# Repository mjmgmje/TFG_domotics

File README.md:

# TFG_domotics
To learn everything about the project, you should read the TFG_domotic.pdf document

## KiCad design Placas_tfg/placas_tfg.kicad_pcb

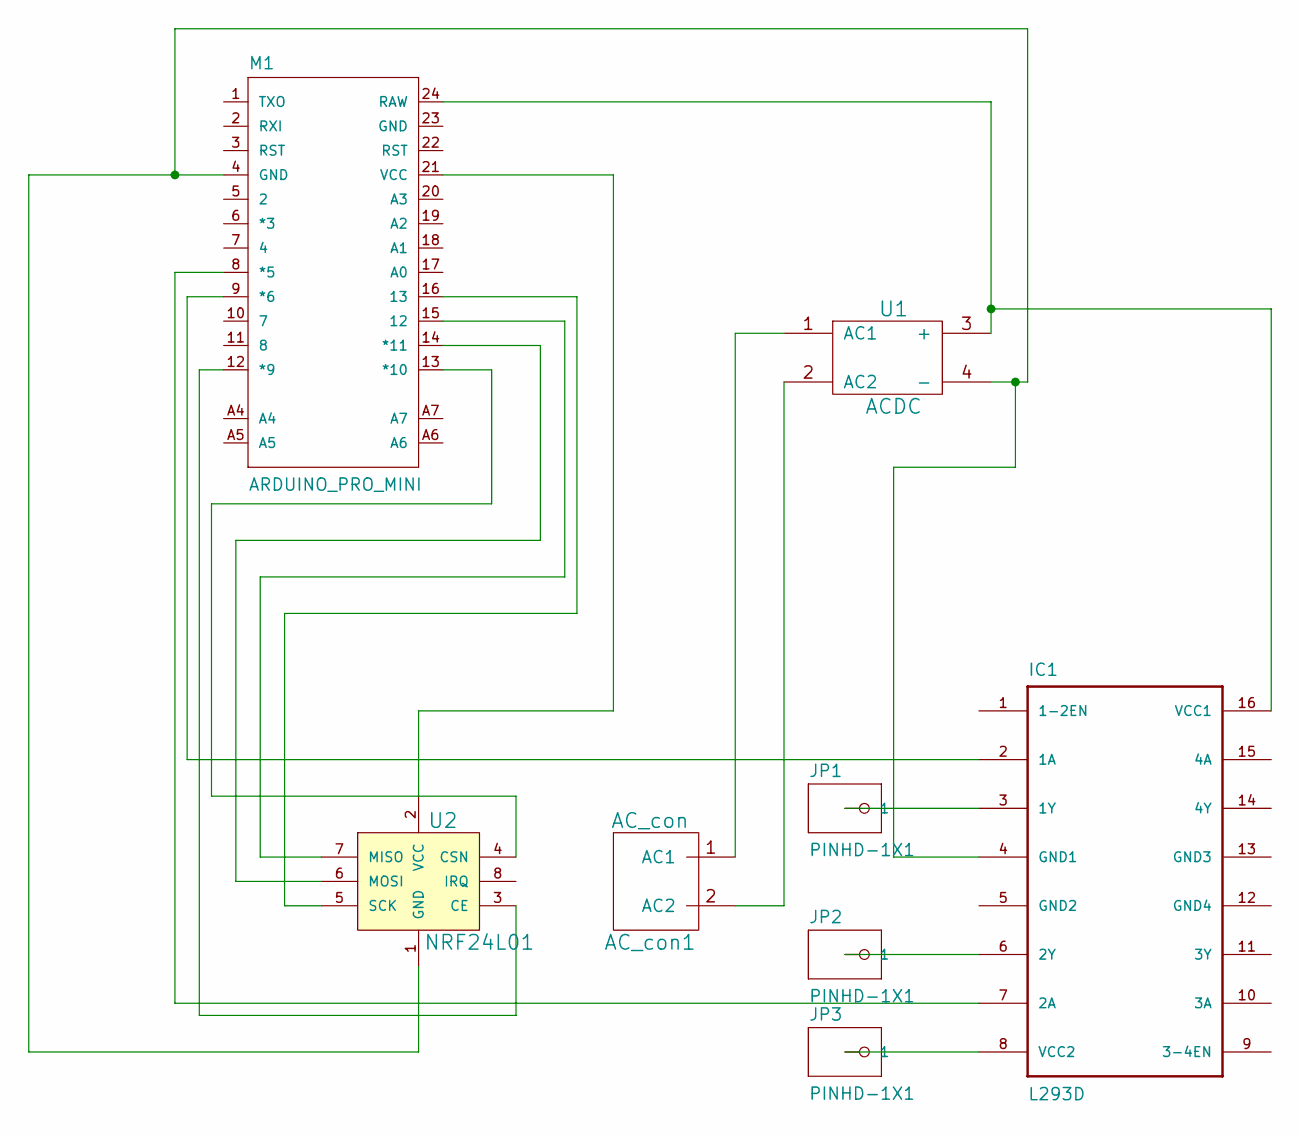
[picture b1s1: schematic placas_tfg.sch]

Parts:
AC_con1: AC_con
IC1: L293D; DIL16
JP1, JP2, JP3: PINHD-1X1; 1X01
M1: ARDUINO_PRO_MINI
U1: ACDC
U2: NRF24L01

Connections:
unnamed: AC_con1.1 (AC1), U1.1 (AC1)
unnamed: AC_con1.2 (AC2), U1.2 (AC2)
unnamed: IC1.2 (1A), M1.9 (*6)
unnamed: IC1.3 (1Y), JP1.1
unnamed: IC1.4 (GND1), M1.4 (GND), U1.4 (-), U2.1 (GND)
unnamed: IC1.6 (2Y), JP2.1
unnamed: IC1.7 (2A), M1.8 (*5)
unnamed: IC1.8 (VCC2), JP3.1
unnamed: IC1.16 (VCC1), M1.24 (RAW), U1.3 (+)
unnamed: M1.12 (*9), U2.3 (CE)
unnamed: M1.13 (*10), U2.4 (CSN)
unnamed: M1.14 (*11), U2.6 (MOSI)
unnamed: M1.15 (12), U2.7 (MISO)
unnamed: M1.16 (13), U2.5 (SCK)
unnamed: M1.21 (VCC), U2.2 (VCC)

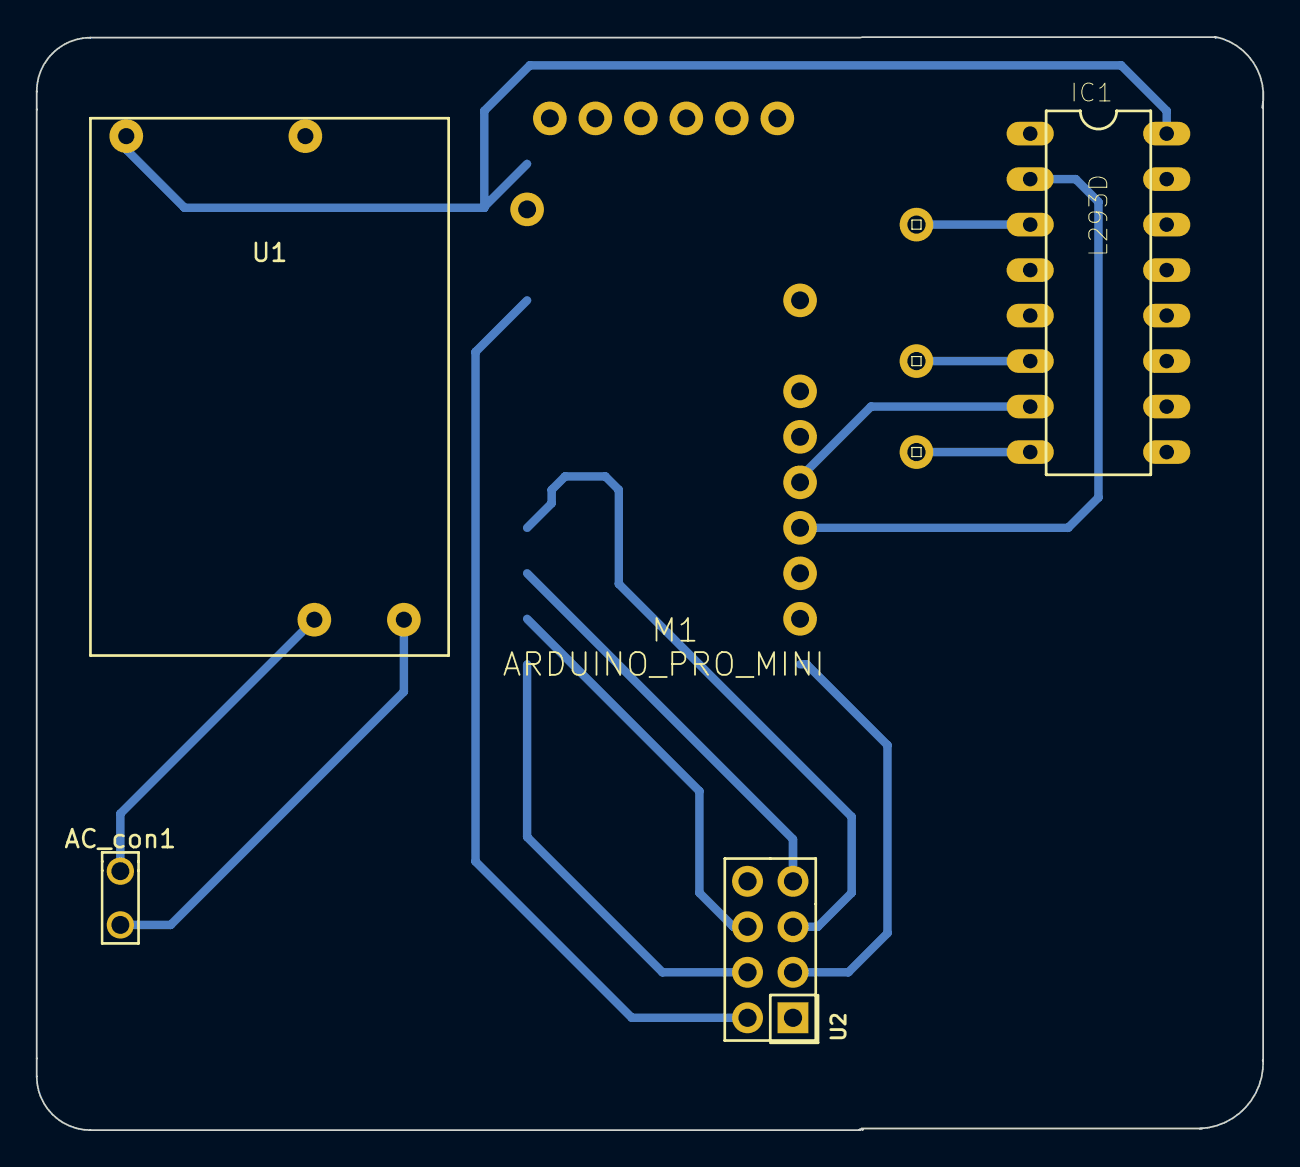
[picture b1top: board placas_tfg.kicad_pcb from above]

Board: 2 copper layers, 68.5 x 61.1 mm, 8 parts (1 on the bottom side), 15 nets.

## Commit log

2017-10-05 tfg commit
